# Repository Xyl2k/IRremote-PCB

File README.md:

IRremote-PCB
============
laser tag cheating device, based on the idea of [BenBurge](http://www.instructables.com/id/BIRRD-A-Laser-Tag-Cheating-Device/?ALLSTEPS)

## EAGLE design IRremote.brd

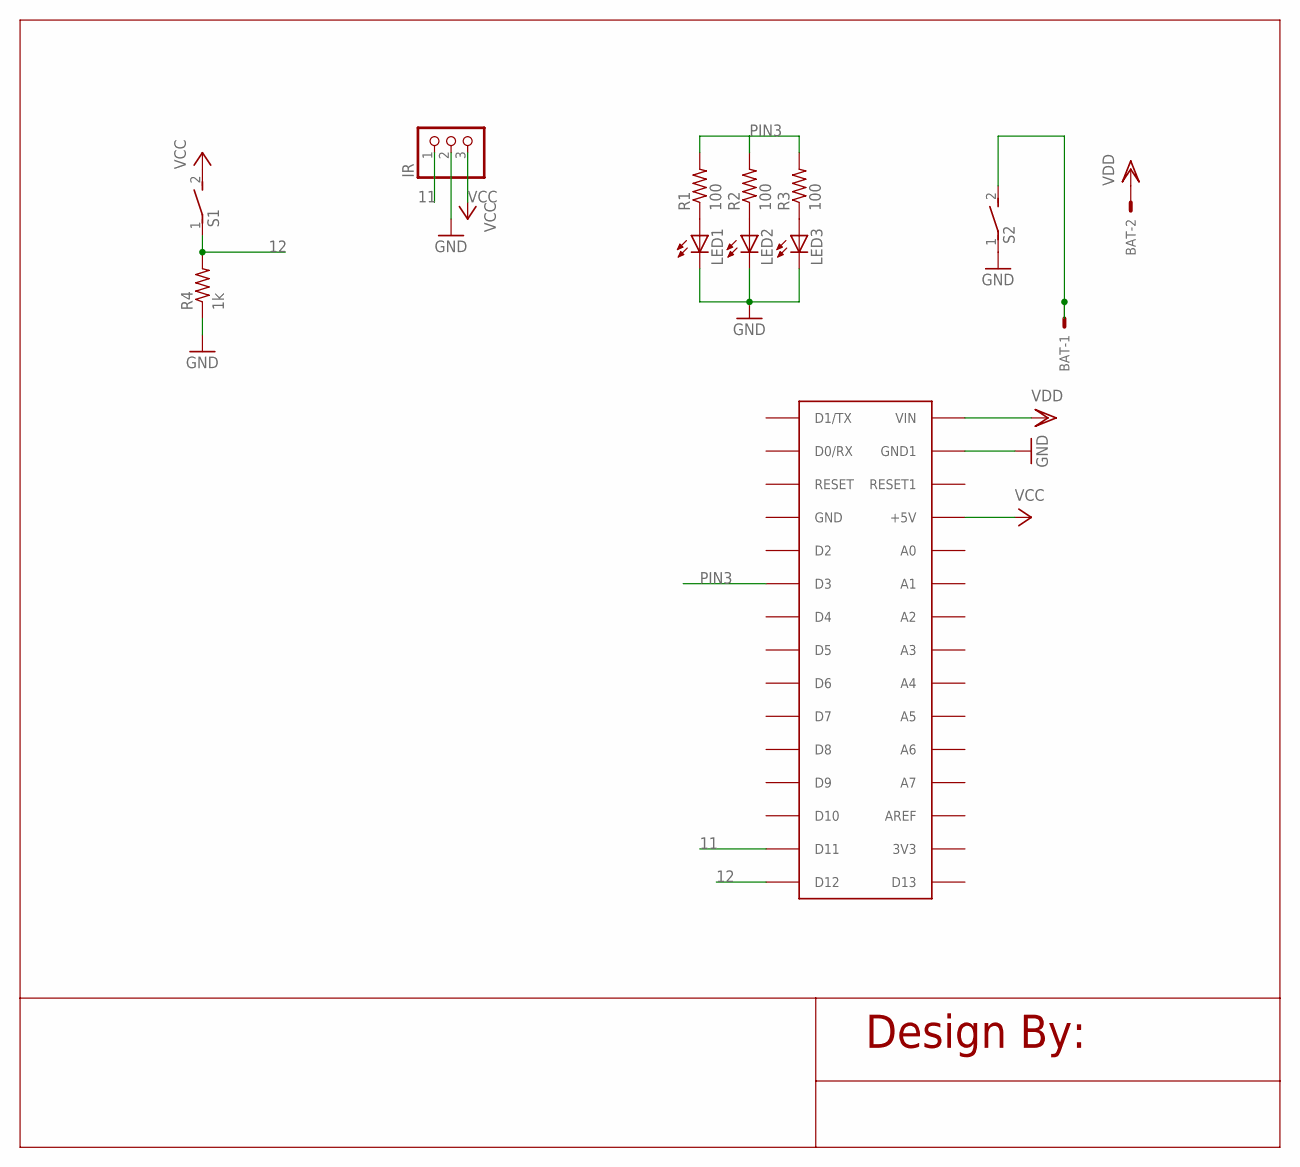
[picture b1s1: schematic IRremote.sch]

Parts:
ARDIUNO-NANO: ARDUINONANO; PDIP-32
BAT: 22-23-2021
IR: PINHD-1X3; 1X03
LED1, LED2, LED3: LED5MM
R1, R2, R3: 100; R0603
R4: 1k; R0603
S1, S2: DS01E; DS-01

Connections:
11: ARDIUNO-NANO.D11, IR.1
12: ARDIUNO-NANO.D12, R4.2, S1.1
GND: ARDIUNO-NANO.GND1, IR.2, LED1.K (C), LED2.K (C), LED3.K (C), R4.1, S2.1
unnamed: LED1.A, R1.1
unnamed: LED2.A, R2.1
unnamed: LED3.A, R3.1
unnamed: BAT.1, S2.2
PIN3: ARDIUNO-NANO.D3, R1.2, R2.2, R3.2
VCC: ARDIUNO-NANO.+5V, IR.3, S1.2
VDD: ARDIUNO-NANO.VIN, BAT.2

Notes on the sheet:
Design By:

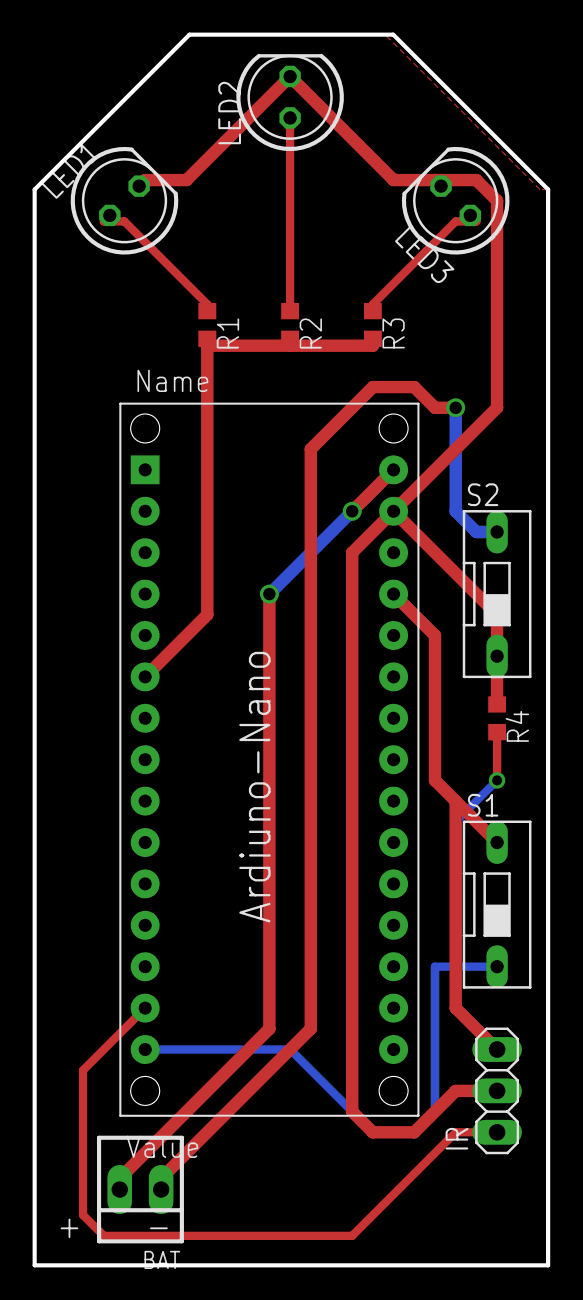
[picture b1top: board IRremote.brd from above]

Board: 2 copper layers, 31.5 x 75.5 mm, 12 parts (0 on the bottom side), 10 nets.

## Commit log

2015-05-02 :space_invader: Added .gitattributes & .gitignore files
2015-05-02 1.0
    1.0
2015-05-02 1.1
    1.1
